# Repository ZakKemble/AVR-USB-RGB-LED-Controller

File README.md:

Dev branch. Working on converting the libUSB stuff to HID so drivers aren't required on Windows. Using <a href="https://github.com/signal11/hidapi">HIDAPI</a>.  

librgbledctrl renamed to librgbled

Everything seems to work on Windows with just a few minor workarounds for some things. Linux still being worked on.

HIDAPI Issues:

Windows:  
open_device() fails if already open (this is ok since usually only 1 thing uses a device) See: https://github.com/signal11/hidapi/issues/138  
hid_get_feature_report() returns data length + 1 for ID, but data starts at \[0\] and last byte is untouched (docs say data starts at \[1\] and \[0\] is the report ID)  
Having a report type INPUT with hid_read() (or hid_write(), whichever youre supposed to use for INPUT, cant remember) causes bits of data to be lost, high bus activity, generally gets all messed up (workaround = use FEATURE type instead)  

Linux:  
HIDRAW backend doesn't see device at all, have to use libusb backend  
open_device() works if already open, but writing/reading fails with "usb 2-2.1: usbfs: process 24733 (rndflasher) did not claim interface 0 before use" (not much of an issue since you'd normally only have a device opened once)  
Enumerate stuff also hangs after the error above, device needs to be reconnected  
If a device is open, calls to hid_enumerate(0, 0) to look for more devices will often mess things up, see above  
hid_get_feature_report() returns data length without + 1 for ID. Data starts at \[0\] (docs say different)  

Windows is Windows 7 x64  
Linux is Debian 7.1 running on VMware.

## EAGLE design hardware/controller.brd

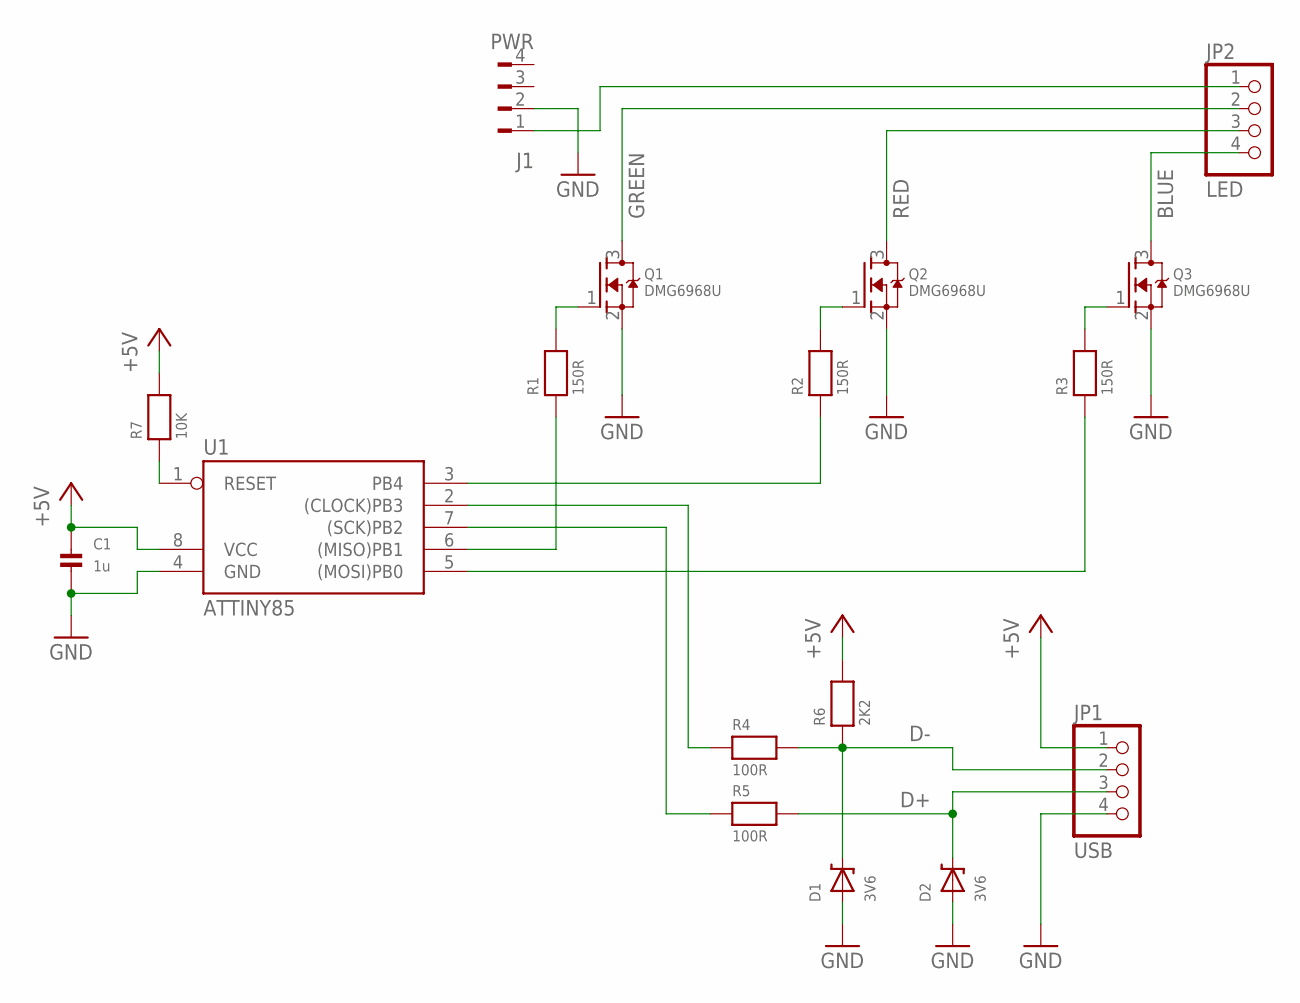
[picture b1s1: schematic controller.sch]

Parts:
C1: 1u; 0805
D1, D2: 3V6; SOD-323
J1: PWR; 827001
JP1: USB; 1X04
JP2: LED; 1X04
Q1, Q2, Q3: DMG6968U; SOT23-W
R1, R2, R3: 150R; 0805
R4, R5: 100R; 0805
R6: 2K2; 0805
R7: 10K; 0805
U1: ATTINY85; SOIC127P798X216-8N

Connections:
+5V: C1.1, JP1.1, R6.2, R7.2, U1.8 (VCC)
BLUE: JP2.4, Q3.3 (D)
D+: D2.C, JP1.3, R5.2
D-: D1.C, JP1.2, R4.2, R6.1
GND: C1.2, D1.A, D2.A, J1.2, JP1.4, Q1.2 (S), Q2.2 (S), Q3.2 (S), U1.4 (GND)
GREEN: JP2.2, Q1.3 (D)
MISO: R1.1, U1.6 ((MISO)PB1)
MOSI: R3.1, U1.5 ((MOSI)PB0)
unnamed: Q1.1 (G), R1.2
unnamed: Q2.1 (G), R2.2
unnamed: Q3.1 (G), R3.2
unnamed: R4.1, U1.2 ((CLOCK)PB3)
unnamed: J1.1, JP2.1
unnamed: R2.1, U1.3 (PB4)
RED: JP2.3, Q2.3 (D)
RST: R7.1, U1.1 (RESET)
SCK: R5.1, U1.7 ((SCK)PB2)

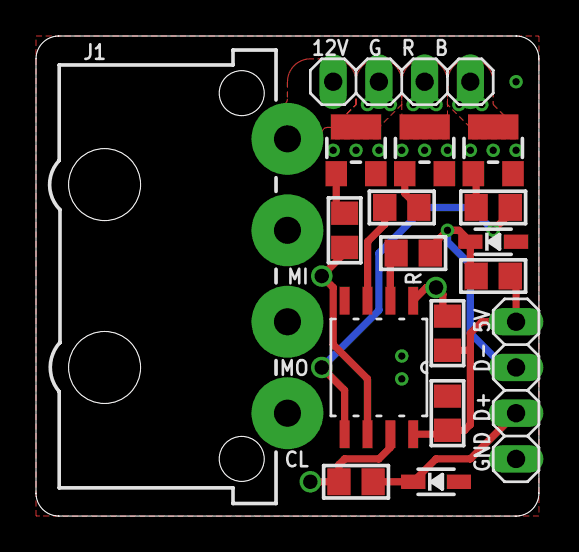
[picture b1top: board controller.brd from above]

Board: 2 copper layers, 27.9 x 26.7 mm, 17 parts (0 on the bottom side), 17 nets.

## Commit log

2013-08-25 Some missing files
2013-08-28 Load of changes
    Lots of stuff; support for multiple devices, C++ wrapper class, updated
    C# .NET wrapper class, updated examples, doxygen docs.
2013-09-01 First pages commit
2013-09-01 Doxygen pages
2014-12-02 Changing libUSB stuff to HID
    Device now enumerates as a HID.
    Lots of lib changes, using HIDAPI instead of libUSB.
    Still a WIP
2014-12-02 Rename Rgbledctrl.cs to Rgbled.cs
2014-12-02 Rename rgbledctrl.h to rgbled.h
2014-12-02 Changing libUSB stuff to HID
    File renames rgbledctrl -> rgbled
2014-12-02 Changing libUSB stuff to HID
    Lib code update
2016-04-09 Readme markdown fix
2020-04-29 Corrected read length

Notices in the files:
parts and their libraries:
microbuilder: This work is placed in the public domain, and may be freely used for commercial and non-commercial work with the following conditions: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
